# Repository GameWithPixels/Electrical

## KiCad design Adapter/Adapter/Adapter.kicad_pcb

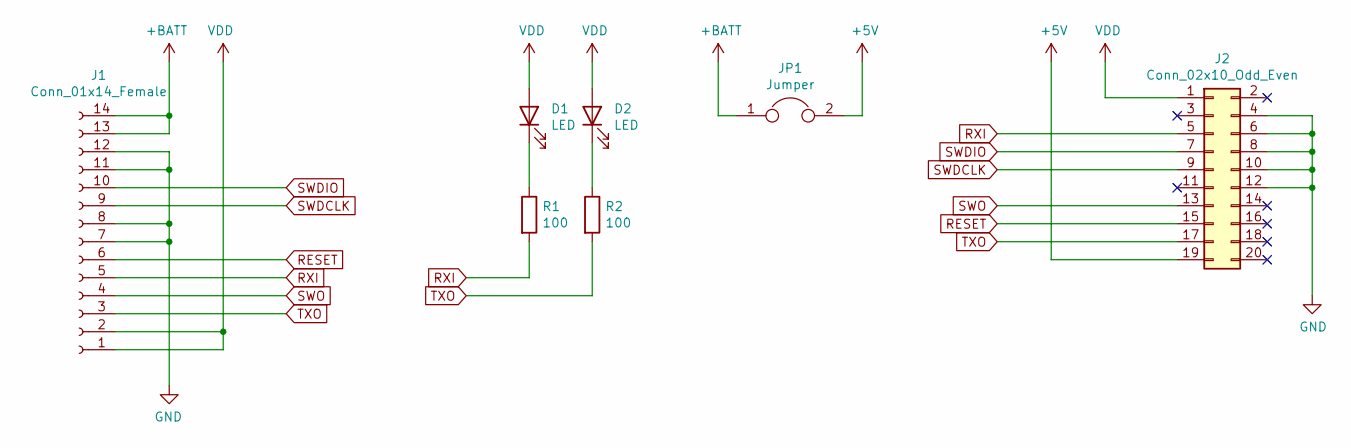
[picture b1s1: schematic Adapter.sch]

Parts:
D1, D2: LED; D_0603_1608Metric; JLCPCB Part Number C72043
J1: Conn_01x14_Female; JUSHUO_FPC_14; JLCPCB Part Number C41302
J2: Conn_02x10_Odd_Even; IDC-Header_2x10_P2.54mm_Vertical
JP1: Jumper; PinHeader_1x02_P2.54mm_Vertical; JLCPCB Part Number C160332
R1, R2: 100; R_0603_1608Metric; JLCPCB Part Number C22775

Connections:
+5V: J2.19, JP1.2
+BATT: J1.13, J1.14, JP1.1
GND: J1.7, J1.8, J1.11, J1.12, J2.4, J2.6, J2.8, J2.10, J2.12
unnamed: D1.1 (K), R1.1
unnamed: D2.1 (K), R2.1
RESET: J1.6, J2.15
RXI: J1.5, J2.5, R1.2
SWDCLK: J1.9, J2.9
SWDIO: J1.10, J2.7
SWO: J1.4, J2.13
TXO: J1.3, J2.17, R2.2
VDD: D1.2 (A), D2.2 (A), J1.1, J1.2, J2.1

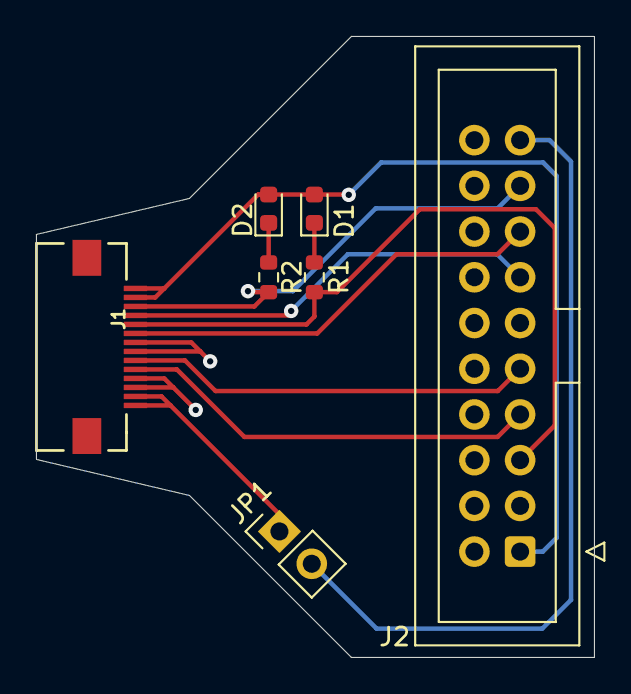
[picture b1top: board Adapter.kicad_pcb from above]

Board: 2 copper layers, 31.0 x 34.5 mm, 7 parts (0 on the bottom side), 12 nets.

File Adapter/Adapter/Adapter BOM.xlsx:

Comment | Designator | Footprint | LCSC Part #
LED | D1, D2 | Diode_SMD:D_0603_1608Metric | C72043
Conn_01x14_Female | J1 | Pixels-dice:JUSHUO_FPC_14 | C41302
Conn_02x10_Odd_Even | J2 | Connector_IDC:IDC-Header_2x10_P2.54mm_Vertical
Jumper | JP1 | Connector_PinHeader_2.54mm:PinHeader_1x02_P2.54mm_Vertical | C160332
100 | R1, R2 | Resistor_SMD:R_0603_1608Metric | C22775

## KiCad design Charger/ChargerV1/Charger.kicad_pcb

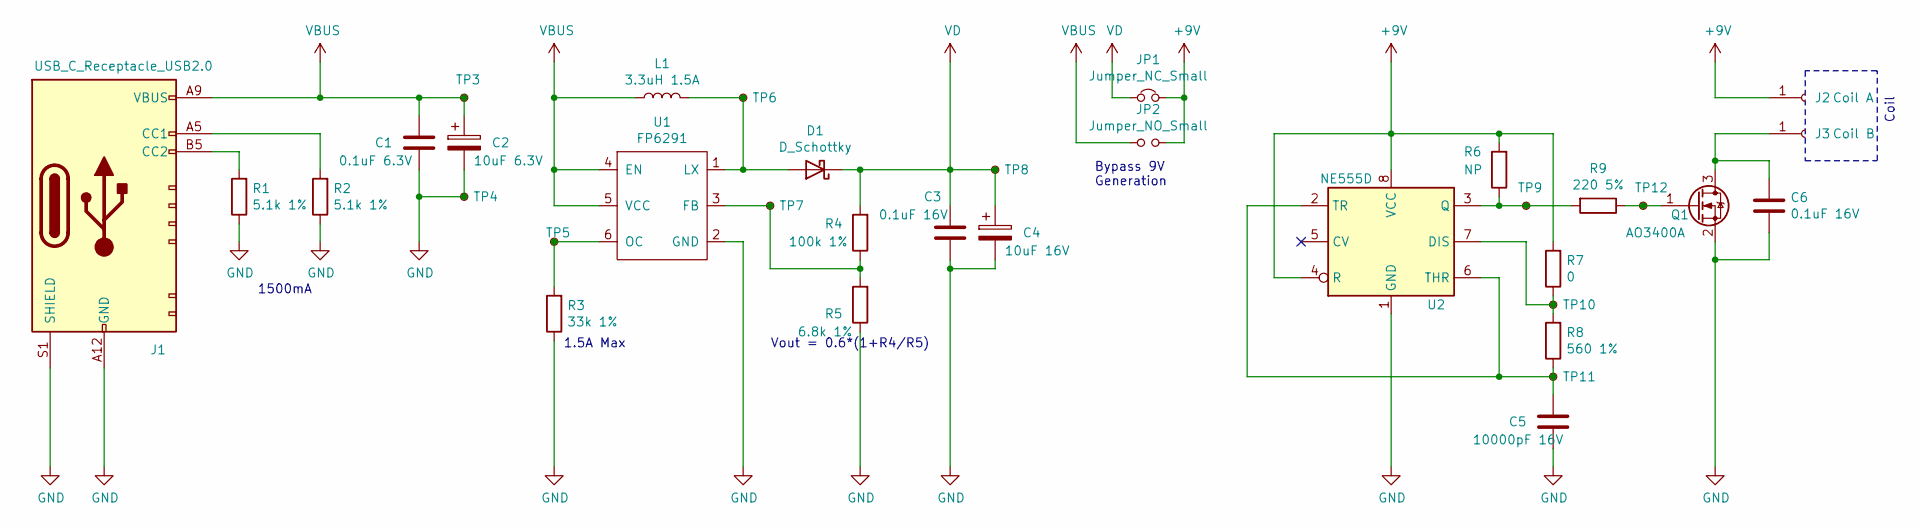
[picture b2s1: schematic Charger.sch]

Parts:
C1: 0.1uF 6.3V; C_0402_1005Metric; Part Number C1005X5R1H104KT000F; LCSC Part Number C361202
C2: 10uF 6.3V; C_0603_1608Metric; Part Number CC0603KRX5R6BB106; LCSC Part Number C326057
C3, C6: 0.1uF 16V; C_0402_1005Metric; Part Number C1005X5R1H104KT000F; LCSC Part Number C361202
C4: 10uF 16V; C_0805_2012Metric; Part Number CL21A106KAYNNNE; LCSC Part Number C15850
C5: 10000pF 16V; C_0402_1005Metric; Part Number C1005X5R1H104KT000F; LCSC Part Number C361202
D1: D_Schottky; D_SOD-123; Part Number B5819W; LCSC Part Number C8598
J1: USB_C_Receptacle_USB2.0; USB-C-SMD_10P-P1.00-L6.8-W8.9; Part Number TYPE-C-31-M-17; LCSC Part Number C283540
J2: Coil A; TestPoint_THTPad_D2.0mm_Drill1.0mm
J3: Coil B; TestPoint_THTPad_D2.0mm_Drill1.0mm
JP1: Jumper_NC_Small; SolderJumper-2_P1.3mm_Bridged_Pad1.0x1.5mm
JP2: Jumper_NO_Small; SolderJumper-2_P1.3mm_Open_Pad1.0x1.5mm
L1: 3.3uH 1.5A; L_1008_2520Metric; Part Number MPH252010C3R3MT; LCSC Part Number C370029
Q1: AO3400A; SOT-23; Part Number AO3400A; LCSC Part Number C344010
R1, R2: 5.1k 1%; R_0402_1005Metric; Part Number 0402WGF5101TCE; LCSC Part Number C25905
R3: 33k 1%; R_0402_1005Metric; Part Number 0402WGF3302TCE; LCSC Part Number C25779
R4: 100k 1%; R_0402_1005Metric; Part Number 0402WGF1003TCE; LCSC Part Number C25741
R5: 6.8k 1%; R_0402_1005Metric; Part Number 0402WGF6801TCE; LCSC Part Number C25917
R6: NP; R_0402_1005Metric; Part Number 0402WGF1003TCE
R7: 0; R_0402_1005Metric; Part Number 0402WGJ0000TCE; LCSC Part Number C21376
R8: 560 1%; R_0402_1005Metric; Part Number 0402WGF5600TCE; LCSC Part Number C25126
R9: 220 5%; R_0402_1005Metric; Part Number 0402WGF2200TCE; LCSC Part Number C25091
TP3, TP4, TP5, TP6, TP7, TP8, TP9, TP10, TP11, TP12: TestPoint_Small; TestPoint_Pad_1.0x1.0mm
U1: FP6291; SOT-23-6; Part Number FP6291LR-G1; LCSC Part Number C18701
U2: NE555D; SOIC-8_3.9x4.9mm_P1.27mm; Part Number NE555DR; LCSC Part Number C7593

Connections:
+9V: J2.1, JP1.2, JP2.2, R6.2, R7.2, U2.4 (R), U2.8 (VCC)
GND: C1.2, C2.2, C3.2, C4.2, C5.2, C6.2, J1.A12 (GND), J1.B12 (GND), J1.S1 (SHIELD), Q1.2 (S), R1.1, R2.1, R3.1, R5.1, TP4.1, U1.2 (GND), U2.1 (GND)
unnamed: C5.1, R8.1, TP11.1, U2.2 (TR), U2.6 (THR)
unnamed: C6.1, J3.1, Q1.3 (D)
unnamed: D1.2 (A), L1.2, TP6.1, U1.1 (LX)
unnamed: J1.A5 (CC1), R2.2
unnamed: J1.B5 (CC2), R1.2
unnamed: Q1.1 (G), R9.1, TP12.1
unnamed: R3.2, TP5.1, U1.6 (OC)
unnamed: R4.1, R5.2, TP7.1, U1.3 (FB)
unnamed: R6.1, R9.2, TP9.1, U2.3 (Q)
unnamed: R7.1, R8.2, TP10.1, U2.7 (DIS)
VBUS: C1.1, C2.1, J1.A9 (VBUS), J1.B9 (VBUS), JP2.1, L1.1, TP3.1, U1.4 (EN), U1.5 (VCC)
VD: C3.1, C4.1, D1.1 (K), JP1.1, R4.2, TP8.1

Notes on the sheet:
1500mA
Coil
Bypass 9V Generation
Vout = 0.6*(1+R4/R5)
1.5A Max

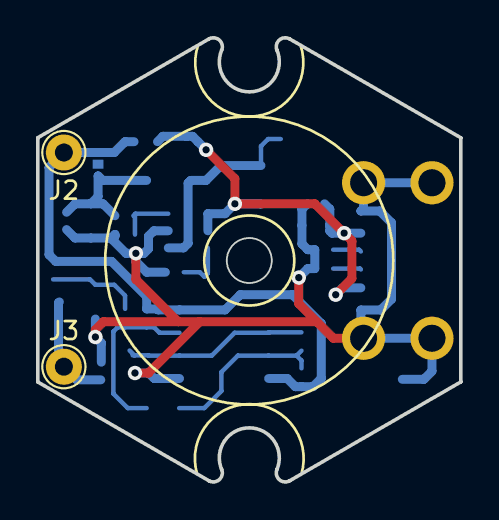
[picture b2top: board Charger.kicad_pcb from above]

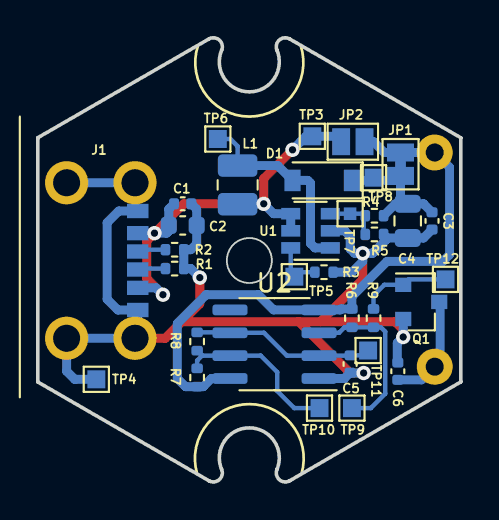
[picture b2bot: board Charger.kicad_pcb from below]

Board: 2 copper layers, 23.5 x 24.7 mm, 35 parts (33 on the bottom side), 14 nets.

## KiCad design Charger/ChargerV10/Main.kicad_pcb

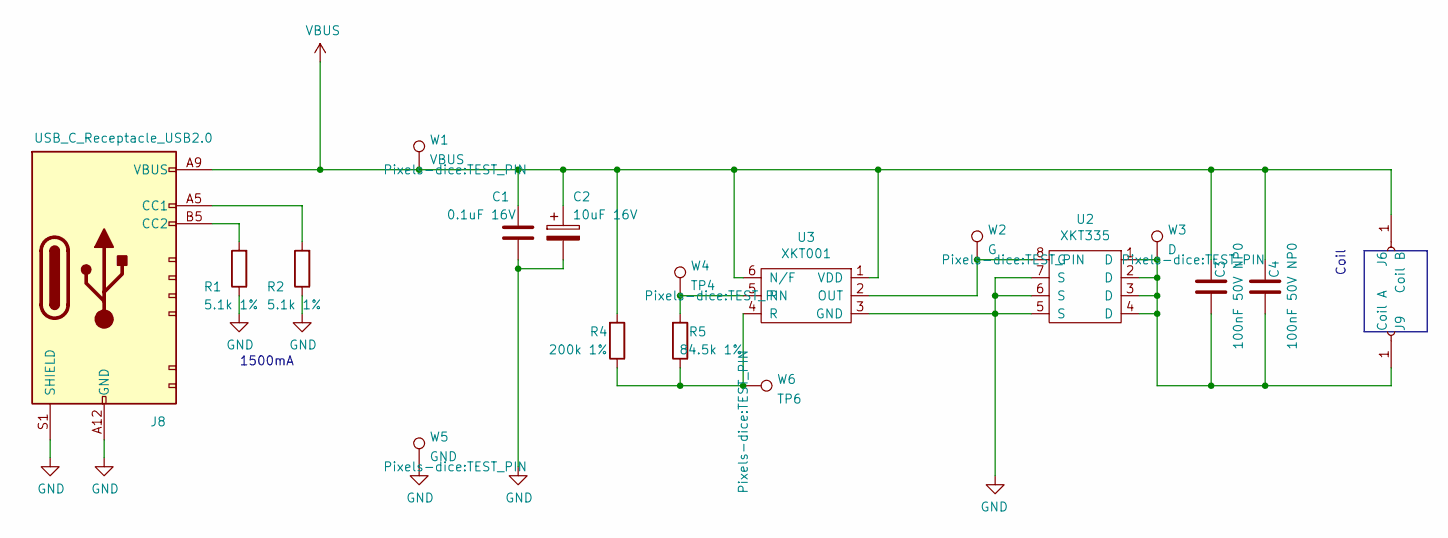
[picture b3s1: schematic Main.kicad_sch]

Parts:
C1: 0.1uF 16V; C_0402_1005Metric; Part Number CL05B104KO5NNNC; LCSC Part Number C1525
C2: 10uF 16V; C_0805_2012Metric; Part Number CL21A106KAYNNNE; LCSC Part Number C15850
C3, C4: 100nF 50V NP0; C_1206_3216Metric; Part Number 1206N104J500CT; LCSC Part Number C170182
J6: Coil B; TestPoint_THTPad_D2.0mm_Drill1.0mm
J8: USB_C_Receptacle_USB2.0; USB-C-SMD_10P-P1.00-L6.8-W8.9; Part Number TYPE-C-31-M-17; LCSC Part Number C283540
J9: Coil A; TestPoint_THTPad_D2.0mm_Drill1.0mm
R1, R2: 5.1k 1%; R_0402_1005Metric; Part Number 0402WGF5101TCE; LCSC Part Number C25905
R4: 200k 1%; R_0402_1005Metric; Part Number 0402WGF2003TCE; LCSC Part Number C25764
R5: 84.5k 1%; R_0402_1005Metric; Part Number 0402WGF8452TCE; LCSC Part Number C26988
U2: XKT335; SO-8_3.9x4.9mm_P1.27mm; Part Number 335
U3: XKT001; SOT-23-6; Part Number 001
W1: VBUS; TEST_PIN
W2: G; TEST_PIN
W3: D; TEST_PIN
W4: TP4; TEST_PIN
W5: GND; TEST_PIN
W6: TP6; TEST_PIN

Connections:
GND: C1.2, C2.2, J8.A12 (GND), J8.B12 (GND), J8.S1 (SHIELD), R1.1, R2.1, U2.5 (S), U2.6 (S), U2.7 (S), U3.3 (GND), W5.1
unnamed: C3.1, C4.1, J9.1, U2.1 (D), U2.2 (D), U2.3 (D), U2.4 (D), W3.1
unnamed: J8.A5 (CC1), R2.2
unnamed: J8.B5 (CC2), R1.2
unnamed: R4.1, R5.1, U3.4 (R), W6.1
unnamed: R5.2, U3.5 (R), W4.1
unnamed: U2.8 (G), U3.2 (OUT), W2.1
VBUS: C1.1, C2.1, C3.2, C4.2, J6.1, J8.A9 (VBUS), J8.B9 (VBUS), R4.2, U3.1 (VDD), U3.6 (N/F), W1.1

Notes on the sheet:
Coil
1500mA

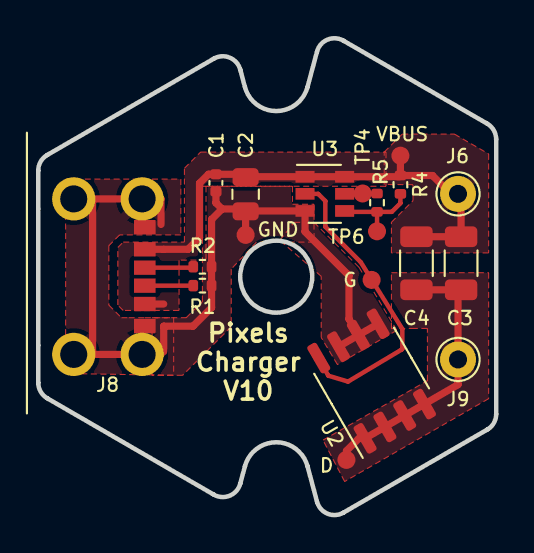
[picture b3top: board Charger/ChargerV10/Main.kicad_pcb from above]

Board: 2 copper layers, 25.4 x 26.5 mm, 19 parts (0 on the bottom side), 8 nets.

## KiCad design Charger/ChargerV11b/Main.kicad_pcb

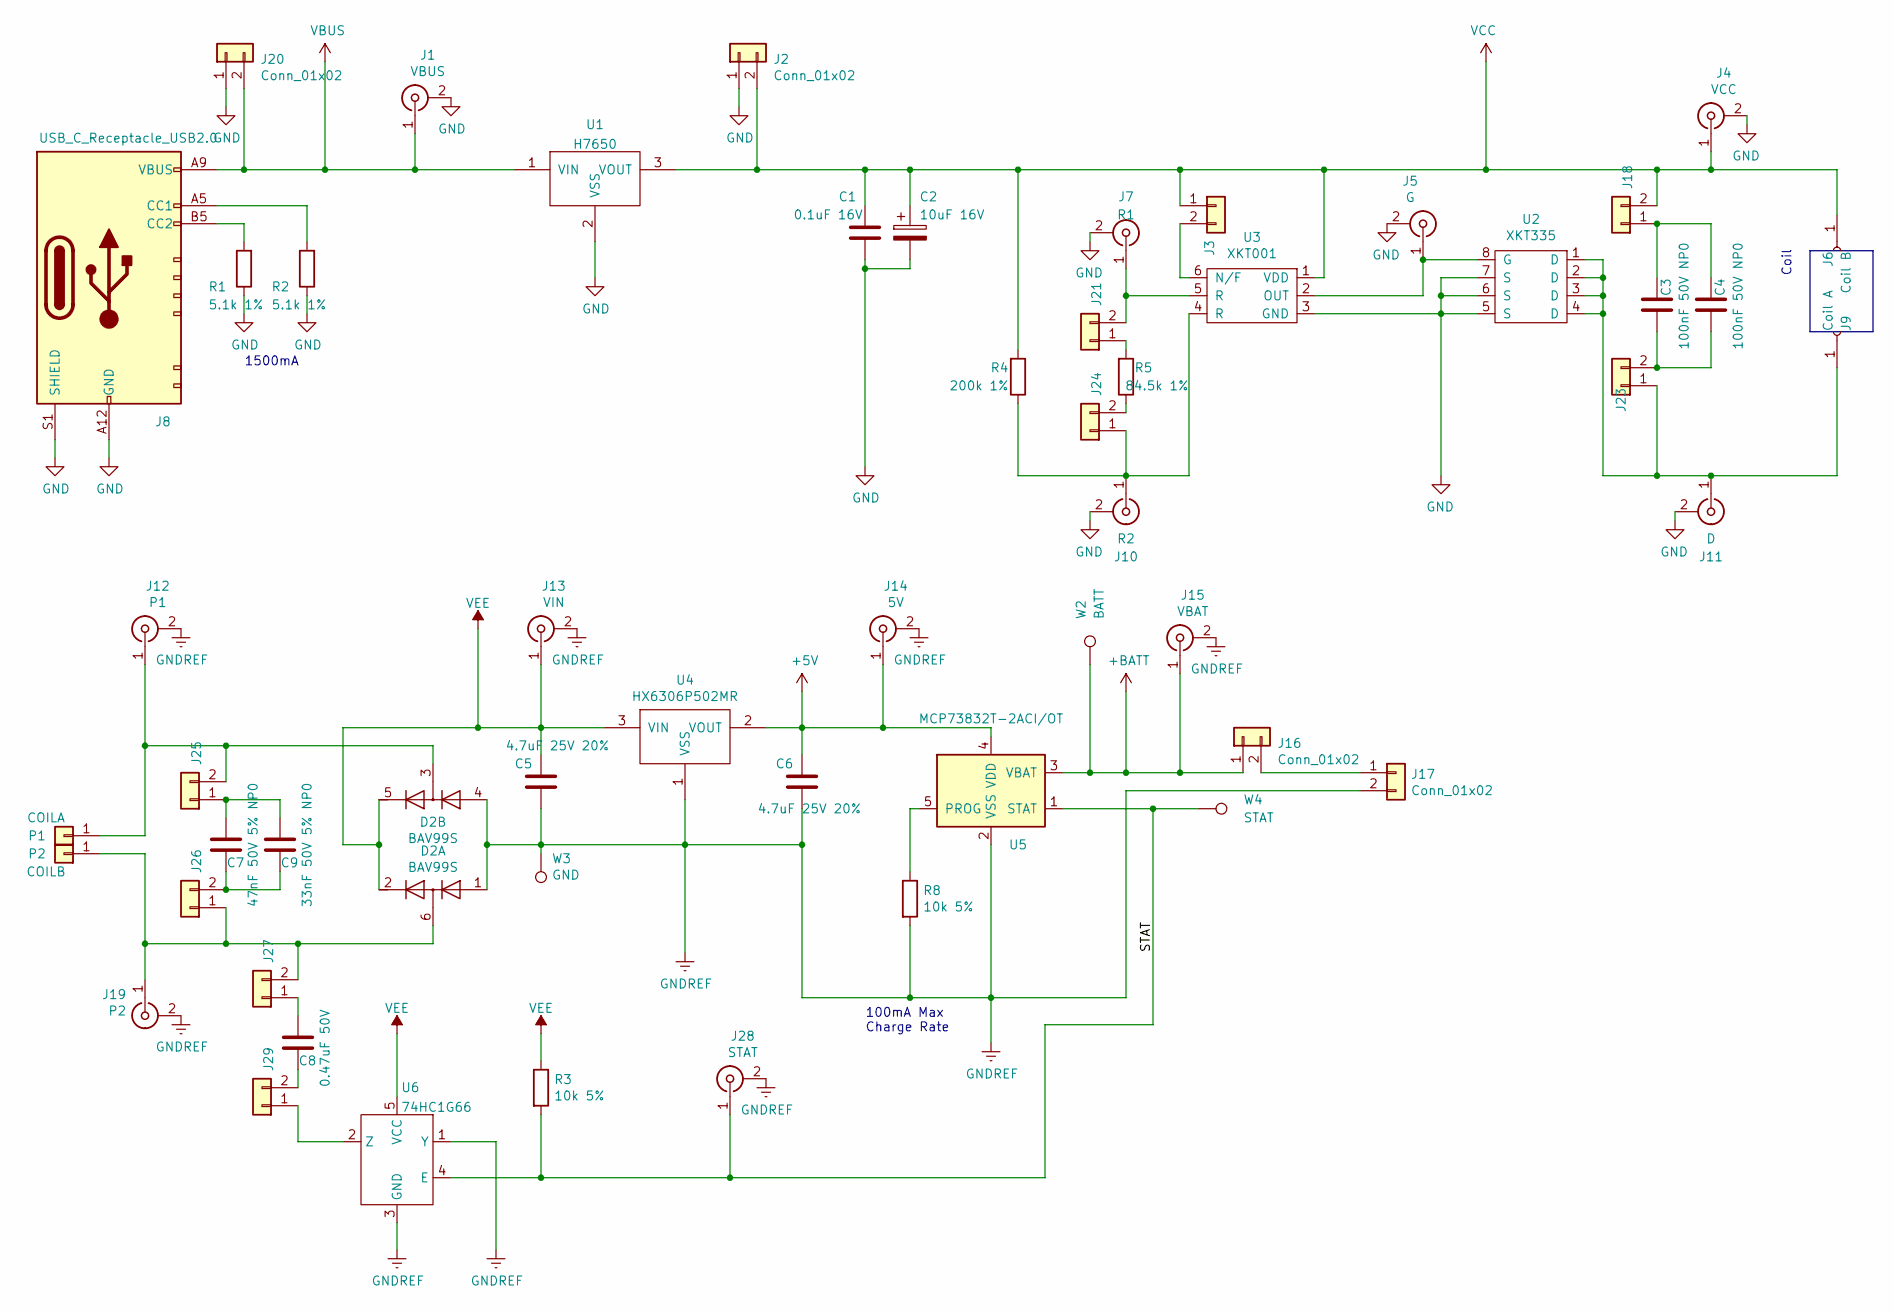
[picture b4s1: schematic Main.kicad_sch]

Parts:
C1: 0.1uF 16V; C_0603_1608Metric; Part Number CL10B104KO8NNNC; LCSC Part Number C66501
C2: 10uF 16V; C_0805_2012Metric; Part Number CL21A106KOQNNNE; LCSC Part Number C1713
C3, C4: 100nF 50V NP0; C_1206_3216Metric; Part Number 1206N104J500CT; LCSC Part Number C170182
C5, C6: 4.7uF 25V 20%; C_0805_2012Metric; Part Number CL21A475KAQNNNE; LCSC Part Number C1779
C7: 47nF 50V 5% NP0; C_1206_3216Metric; Part Number GRM31M5C1H473JA01L; LCSC Part Number C21812
C8: 0.47uF 50V; C_0603_1608Metric; Part Number CL10F474ZB8NNNC; LCSC Part Number C296719
C9: 33nF 50V 5% NP0; C_1206_3216Metric; Part Number GRM3195C1H333JA01D; LCSC Part Number C97930
D2: BAV99S; SOT-363_SC-70-6; Part Number BAV99SH6327XTSA1; LCSC Part Number C68987
J1: VBUS; U.FL-R-SMT-1(80); Part Number U.FL-R-SMT-1(80); LCSC Part Number C88374
J2, J3, J16, J18, J20, J21, J23, J24, J25, J26, J27, J29: Conn_01x02; PinHeader_1x02_P2.54mm_Vertical_SMD_Pin1Right; Part Number X6511WVS-02H-C60D48R1; LCSC Part Number C2883799
J4: VCC; U.FL-R-SMT-1(80); Part Number U.FL-R-SMT-1(80); LCSC Part Number C88374
J5: G; U.FL-R-SMT-1(80); Part Number U.FL-R-SMT-1(80); LCSC Part Number C88374
J6: Coil B; TestPoint_THTPad_D2.0mm_Drill1.0mm
J7: R1; U.FL-R-SMT-1(80); Part Number U.FL-R-SMT-1(80); LCSC Part Number C88374
J8: USB_C_Receptacle_USB2.0; USB-C-SMD_10P-P1.00-L6.8-W8.9; Part Number TYPE-C-31-M-17; LCSC Part Number C283540
J9: Coil A; TestPoint_THTPad_D2.0mm_Drill1.0mm
J10: R2; U.FL-R-SMT-1(80); Part Number U.FL-R-SMT-1(80); LCSC Part Number C88374
J11: D; U.FL-R-SMT-1(80); Part Number U.FL-R-SMT-1(80); LCSC Part Number C88374
J12: P1; U.FL-R-SMT-1(80); Part Number U.FL-R-SMT-1(80); LCSC Part Number C88374
J13: VIN; U.FL-R-SMT-1(80); Part Number U.FL-R-SMT-1(80); LCSC Part Number C88374
J14: 5V; U.FL-R-SMT-1(80); Part Number U.FL-R-SMT-1(80); LCSC Part Number C88374
J15: VBAT; U.FL-R-SMT-1(80); Part Number U.FL-R-SMT-1(80); LCSC Part Number C88374
J17: Conn_01x02; Hongjie 10100 Connector
J19: P2; U.FL-R-SMT-1(80); Part Number U.FL-R-SMT-1(80); LCSC Part Number C88374
J28: STAT; U.FL-R-SMT-1(80); Part Number U.FL-R-SMT-1(80); LCSC Part Number C88374
P1: COILA; TestPoint_THTPad_D1.5mm_Drill0.7mm
P2: COILB; TestPoint_THTPad_D1.5mm_Drill0.7mm
R1, R2: 5.1k 1%; R_0402_1005Metric; Part Number 0402WGF5101TCE; LCSC Part Number C25905
R3, R8: 10k 5%; R_0603_1608Metric; Part Number 0603WAF1002T5E; LCSC Part Number C25804
R4: 200k 1%; R_0603_1608Metric; Part Number 0603WAF2003T5E; LCSC Part Number C25811
R5: 84.5k 1%; R_0603_1608Metric; Part Number 0603WAF8452T5E; LCSC Part Number C23118
U1: H7650; SOT-223; Part Number H7650-40GR; LCSC Part Number C411047
U2: XKT335; SO-8_3.9x4.9mm_P1.27mm
U3: XKT001; SOT-23-6
U4: HX6306P502MR; SOT-23; Part Number PJ75AL50SA; LCSC Part Number C411735
U5: MCP73832T-2ACI/OT; SOT-23-5; Part Number MCP73832T-2ACI/OT; LCSC Part Number C38066
U6: 74HC1G66; SC-74A; Part Number 74HC1G66GV,125; LCSC Part Number C89412
W2: BATT; TestPoint_Pad_1.0x1.0mm
W3: GND; TestPoint_Pad_1.0x1.0mm
W4: STAT; TestPoint_Pad_1.0x1.0mm

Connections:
+5V: C6.1, J14.1 (In), U4.2 (VOUT), U5.4 (VDD)
+BATT: J15.1 (In), J16.1, U5.3 (VBAT), W2.1
/STAT: J28.1 (In), R3.2, U5.1 (STAT), U6.4 (E), W4.1
GND: C1.2, C2.2, J1.2 (Ext), J2.1, J4.2 (Ext), J5.2 (Ext), J7.2 (Ext), J8.A12 (GND), J8.B12 (GND), J8.S1 (SHIELD), J10.2 (Ext), J11.2 (Ext), J20.1, R1.1, R2.1, U1.2 (VSS), U2.5 (S), U2.6 (S), U2.7 (S), U3.3 (GND)
GNDREF: C5.2, C6.2, D2.1 (A1), D2.4 (A3), J12.2 (Ext), J13.2 (Ext), J14.2 (Ext), J15.2 (Ext), J17.2, J19.2 (Ext), J28.2 (Ext), R8.2, U4.1 (VSS), U5.2 (VSS), U6.1 (Y), U6.3 (GND), W3.1
unnamed: C3.1, C4.1, J23.2
unnamed: C3.2, C4.2, J18.1
unnamed: C7.1, C9.1, J25.1
unnamed: C7.2, C9.2, J26.2
unnamed: C8.1, J27.1
unnamed: C8.2, J29.2
unnamed: D2.3 (K1A2), J12.1 (In), J25.2, P1.1
unnamed: D2.6 (K3A4), J19.1 (In), J26.1, J27.2, P2.1
unnamed: J5.1 (In), U2.8 (G), U3.2 (OUT)
unnamed: J7.1 (In), J21.2, U3.5 (R)
unnamed: J8.A5 (CC1), R2.2
unnamed: J8.B5 (CC2), R1.2
unnamed: J9.1, J11.1 (In), J23.1, U2.1 (D), U2.2 (D), U2.3 (D), U2.4 (D)
unnamed: J10.1 (In), J24.1, R4.1, U3.4 (R)
unnamed: J16.2, J17.1
unnamed: J29.1, U6.2 (Z)
unnamed: J24.2, R5.1
unnamed: J21.1, R5.2
unnamed: J3.2, U3.6 (N/F)
unnamed: R8.1, U5.5 (PROG)
VBUS: J1.1 (In), J8.A9 (VBUS), J8.B9 (VBUS), J20.2, U1.1 (VIN)
VCC: C1.1, C2.1, J2.2, J3.1, J4.1 (In), J6.1, J18.2, R4.2, U1.3 (VOUT), U3.1 (VDD)
VEE: C5.1, D2.2 (K2), D2.5 (K4), J13.1 (In), R3.1, U4.3 (VIN), U6.5 (VCC)

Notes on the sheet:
100mA Max Charge Rate
1500mA
Coil

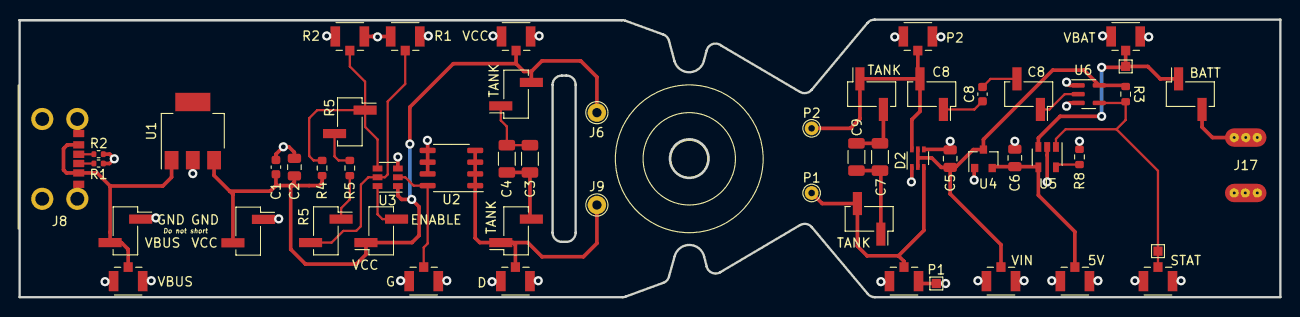
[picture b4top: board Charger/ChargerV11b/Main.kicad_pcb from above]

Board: 2 copper layers, 136.5 x 30.1 mm, 55 parts (0 on the bottom side), 28 nets.
